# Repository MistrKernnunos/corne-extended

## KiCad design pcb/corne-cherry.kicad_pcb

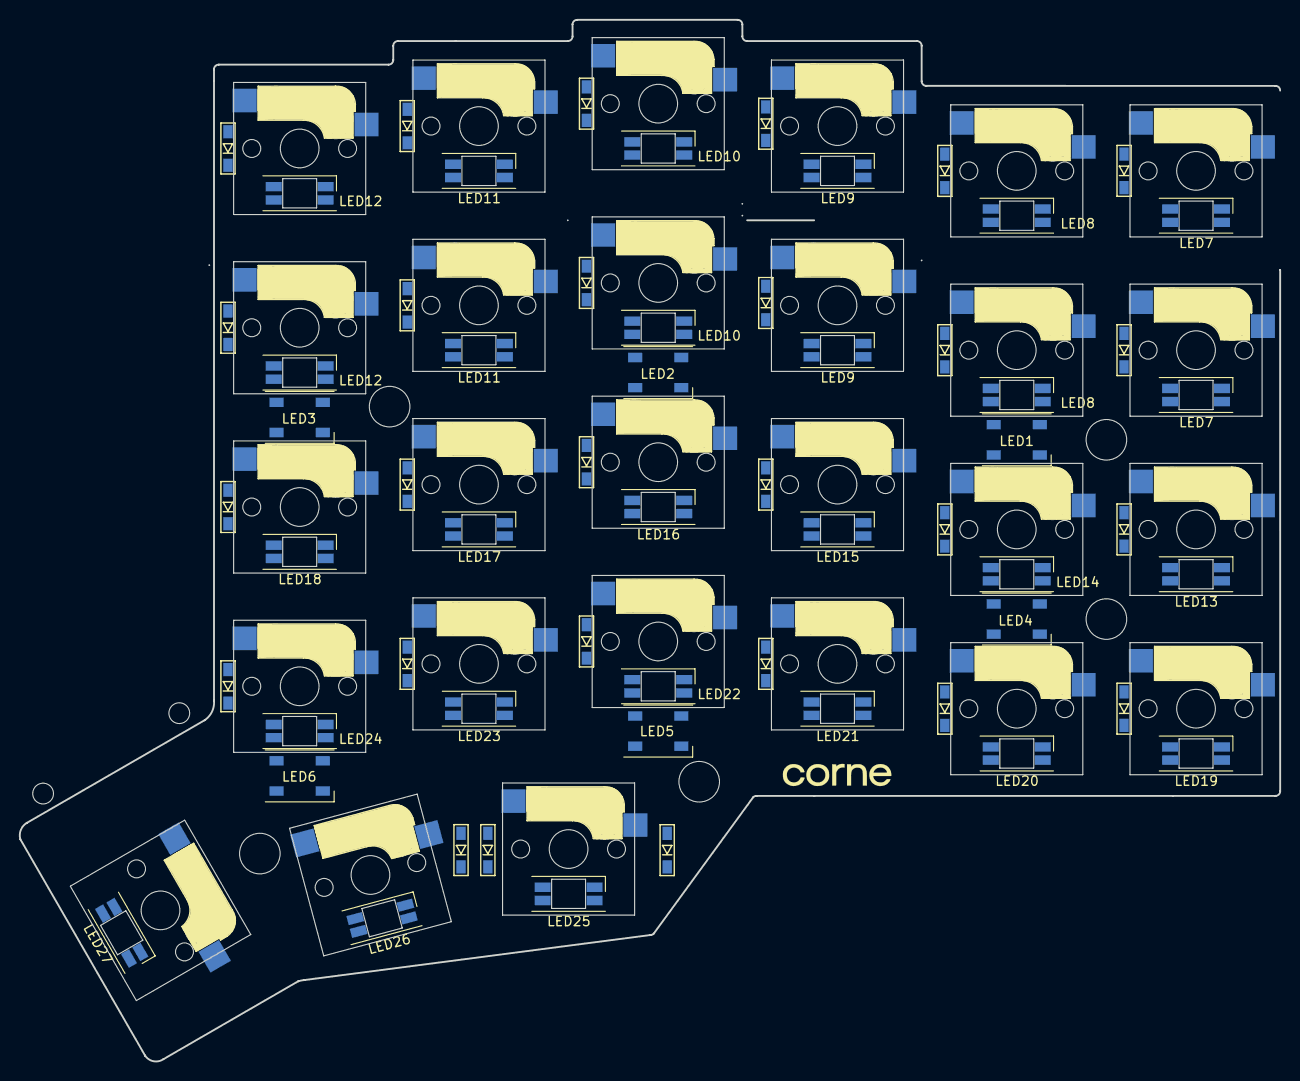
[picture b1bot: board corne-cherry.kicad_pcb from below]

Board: 2 copper layers, 133.6 x 110.4 mm, 94 parts (60 on the bottom side), 45 nets, no tracks yet.

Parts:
D1, D1#2, D2, D2#2, D3, D3#2, D4, D4#2, D5, D5#2, D6, D6#2, D7, D8, D9, D10, D11, D12, D13, D14, D15, D16, D17, D18, D19, D20, D21: D; D3_SMD_v2
LED1, LED2, LED3, LED4, LED5, LED6: WS2812B; LED_WS2812B_PLCC4_5.0x5.0mm_P3.2mm
LED7, LED7#2, LED8, LED8#2, LED9, LED9#2, LED10, LED10#2, LED11, LED11#2, LED12, LED12#2, LED13, LED14, LED15, LED16, LED17, LED18, LED19, LED20, LED21, LED22, LED23, LED24, LED25, LED26, LED27: YS-SK6812MINI-E
Ref**: Val**; M2_HOLE_v2
Ref**#2, Ref**#3, Ref**#4, Ref**#5, Ref**#6, Ref**#7: Val**; M2_HOLE_v2
SW1, SW1#2, SW2, SW2#2, SW3, SW3#2, SW4, SW4#2, SW5, SW5#2, SW6, SW6#2, SW7, SW8, SW9, SW10, SW11, SW12, SW13, SW14, SW15, SW16, SW17, SW18, SW19, SW20, SW21: SW_PUSH; CherryMX_Hotswap

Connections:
GND: LED1.3, LED2.3, LED3.3, LED4.3, LED5.3, LED6.3, LED7.3, LED7#2.3, LED8.3, LED8#2.3, LED9.3, LED9#2.3, LED10.3, LED10#2.3, LED11.3, LED11#2.3, LED12.3, LED12#2.3, LED13.3, LED14.3, LED15.3, LED16.3, LED17.3, LED18.3, LED19.3, LED20.3, LED21.3, LED22.3, LED23.3, LED24.3, LED25.3, LED26.3, LED27.3
unnamed: D1.2, D1#2.2, SW1#2.2
unnamed: D2.2, D2#2.2, SW2#2.2
unnamed: D3.2, D3#2.2, SW3#2.2
unnamed: D4.2, D4#2.2, SW4#2.2
unnamed: D5.2, D5#2.2, SW5#2.2
unnamed: D6.2 (A), D6#2.2 (A), SW6.2, SW6#2.2
unnamed: D12.2 (A), SW12.2
unnamed: D18.2 (A), SW18.2
unnamed: D21.2 (A), SW21.2
unnamed: LED1.2, LED4.4
unnamed: LED1.4, LED2.2
unnamed: LED2.4, LED3.2
unnamed: LED4.2, LED5.4
unnamed: LED5.2, LED6.4
unnamed: LED7.4, LED7#2.4, LED8.2, LED8#2.2
unnamed: LED9.4, LED9#2.4, LED10.2, LED10#2.2
unnamed: LED10.4, LED10#2.4, LED16.2
unnamed: LED11.2, LED11#2.2, LED17.4
unnamed: LED11.4, LED11#2.4, LED12.2, LED12#2.2
unnamed: LED12.4, LED12#2.4, LED18.2
unnamed: LED13.2, LED19.4
unnamed: LED7.2, LED7#2.2, LED13.4
unnamed: LED8.4, LED8#2.4, LED14.2
unnamed: LED14.4, LED20.2
unnamed: LED15.2, LED21.4
unnamed: LED9.2, LED9#2.2, LED15.4
unnamed: LED16.4, LED22.2
unnamed: LED17.2, LED23.4
unnamed: LED18.4, LED24.2
unnamed: LED20.4, LED21.2
unnamed: LED22.4, LED25.2
unnamed: LED23.2, LED26.4
unnamed: LED24.4, LED27.2
unnamed: LED25.4, LED26.2
unnamed: LED6.2, LED27.4
unnamed: SW16.1, SW19.1
VCC: LED1.1, LED2.1, LED3.1, LED4.1, LED5.1, LED6.1, LED7.1, LED7#2.1, LED8.1, LED8#2.1, LED9.1, LED9#2.1, LED10.1, LED10#2.1, LED11.1, LED11#2.1, LED12.1, LED12#2.1, LED13.1, LED14.1, LED15.1, LED16.1, LED17.1, LED18.1, LED19.1, LED20.1, LED21.1, LED22.1, LED23.1, LED24.1, LED25.1, LED26.1, LED27.1
col0: SW1.1, SW1#2.1, SW7.1, SW13.1
col1: SW2.1, SW2#2.1, SW8.1, SW14.1
col2: SW3.1, SW3#2.1, SW9.1, SW15.1
row0: D1.1, D1#2.1, D2.1, D2#2.1, D3.1, D3#2.1, D4.1, D4#2.1, D5.1, D5#2.1
row1: D7.1, D8.1, D9.1, D10.1, D11.1
row2: D13.1, D14.1, D15.1, D16.1, D17.1
row3: D19.1, D20.1

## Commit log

2022-08-11 Update keymaps
2022-08-11 sfhasjfd
2022-08-11 move to config
2022-12-25 it is working
